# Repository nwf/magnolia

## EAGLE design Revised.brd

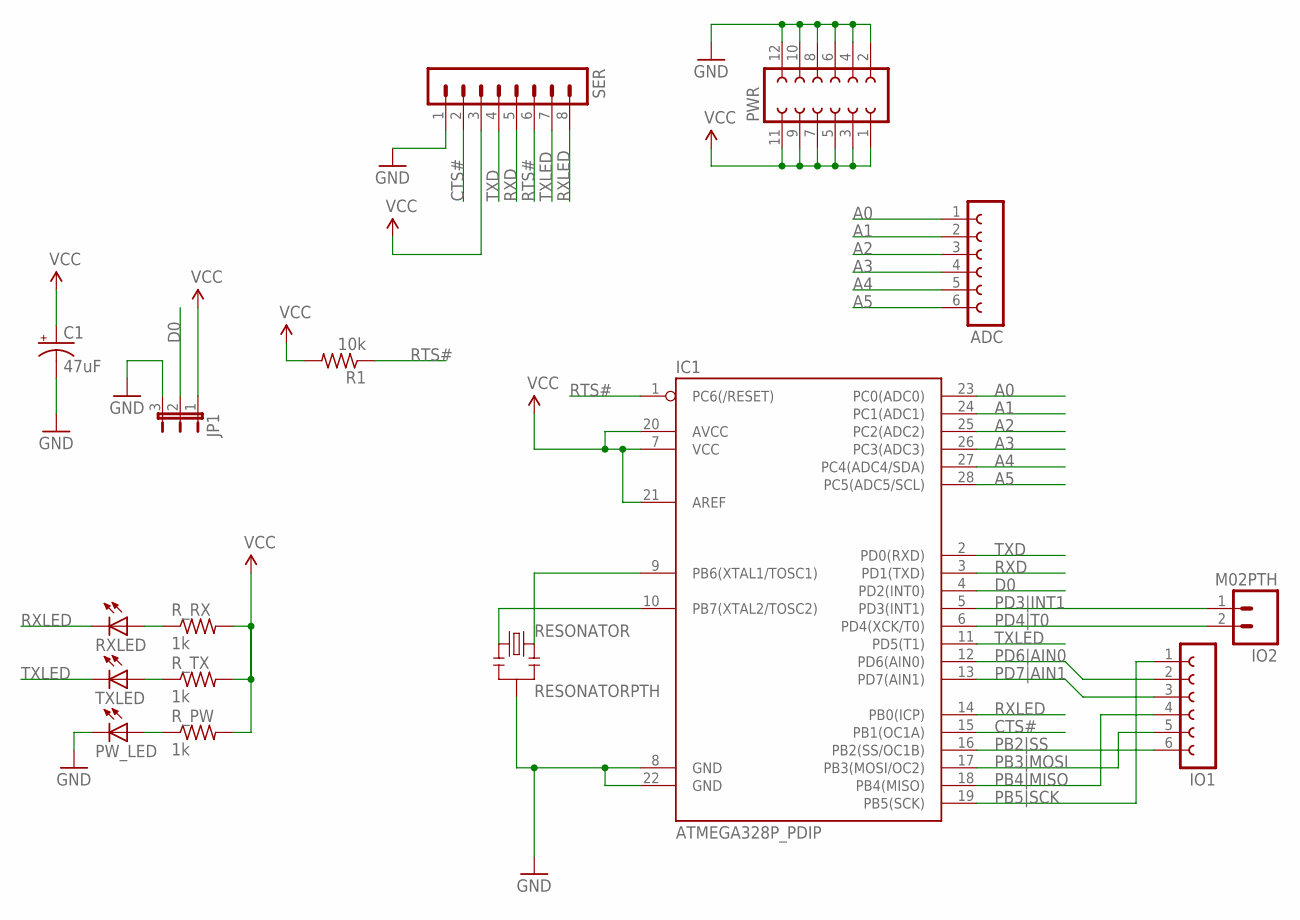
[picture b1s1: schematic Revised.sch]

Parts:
ADC: FE06-1; FE06
C1: 47uF; E2,5-6E
IC1: ATMEGA328P_PDIP; DIL28-3
IO1: FE06-1; FE06
IO2: M02PTH; 1X02
JP1: JP2E; JP2
PWR: FE06-2
PW_LED: LED5MM
R1: 10k; R0805
RESONATOR: RESONATORPTH; RESONATOR-PTH
RXLED: LED5MM
R_PW: 1k; R0805
R_RX: 1k; R0805
R_TX: 1k; R0805
SER: MA08-1W
TXLED: LED5MM

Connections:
A0: ADC.1, IC1.23 (PC0(ADC0))
A1: ADC.2, IC1.24 (PC1(ADC1))
A2: ADC.3, IC1.25 (PC2(ADC2))
A3: ADC.4, IC1.26 (PC3(ADC3))
A4: ADC.5, IC1.27 (PC4(ADC4/SDA))
A5: ADC.6, IC1.28 (PC5(ADC5/SCL))
CTS#: IC1.15 (PB1(OC1A)), SER.2
D0: IC1.4 (PD2(INT0)), JP1.2
GND: C1.-, IC1.8 (GND), IC1.22 (GND), JP1.3, PWR.2, PWR.4, PWR.6, PWR.8, PWR.10, PWR.12, PW_LED.K (C), RESONATOR.2, SER.1
unnamed: IC1.9 (PB6(XTAL1/TOSC1)), RESONATOR.3
unnamed: IC1.10 (PB7(XTAL2/TOSC2)), RESONATOR.1
unnamed: R_TX.1, TXLED.A
unnamed: RXLED.A, R_RX.1
unnamed: PW_LED.A, R_PW.1
PB2|SS: IC1.16 (PB2(SS/OC1B)), IO1.6
PB3|MOSI: IC1.17 (PB3(MOSI/OC2)), IO1.5
PB4|MISO: IC1.18 (PB4(MISO)), IO1.4
PB5|SCK: IC1.19 (PB5(SCK)), IO1.1
PD3|INT1: IC1.5 (PD3(INT1)), IO2.1
PD4|T0: IC1.6 (PD4(XCK/T0)), IO2.2
PD6|AIN0: IC1.12 (PD6(AIN0)), IO1.2
PD7|AIN1: IC1.13 (PD7(AIN1)), IO1.3
RTS#: IC1.1 (PC6(/RESET)), R1.1, SER.6
RXD: IC1.3 (PD1(TXD)), SER.5
RXLED: IC1.14 (PB0(ICP)), RXLED.K (C), SER.8
TXD: IC1.2 (PD0(RXD)), SER.4
TXLED: IC1.11 (PD5(T1)), SER.7, TXLED.K (C)
VCC: C1.+, IC1.7 (VCC), IC1.20 (AVCC), IC1.21 (AREF), JP1.1, PWR.1, PWR.3, PWR.5, PWR.7, PWR.9, PWR.11, R1.2, R_PW.2, R_RX.2, R_TX.2, SER.3

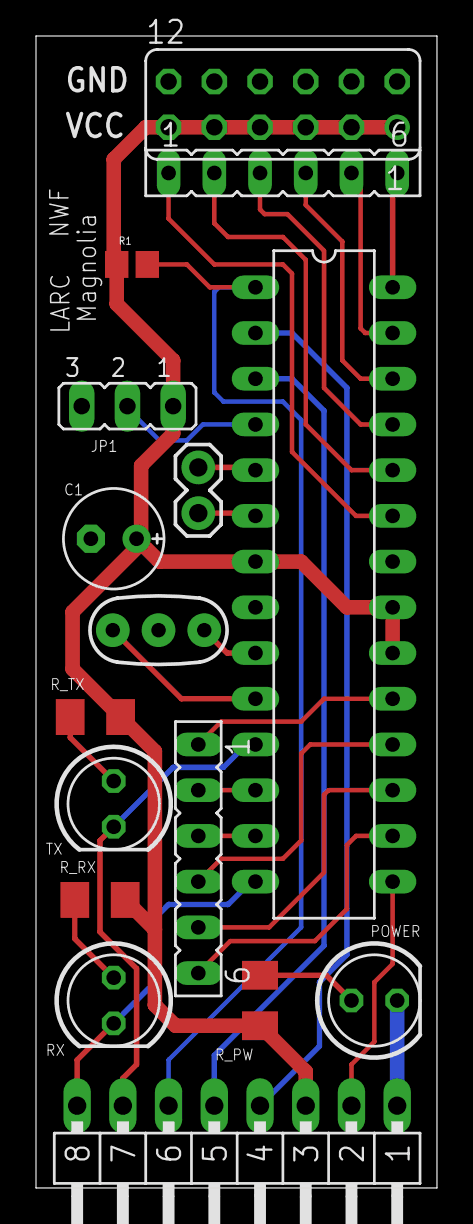
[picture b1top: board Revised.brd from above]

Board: 2 copper layers, 22.3 x 64.0 mm, 16 parts (0 on the bottom side), 28 nets.

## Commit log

2014-03-22 Checkin shipped brd file
2014-03-22 Derived sch from shipped brd file
2014-03-22 Add proposed revision versions
2014-03-22 Small tweaks
    Remove capacitive coupling to RST#, which should enable debugWIRE
    Thicken the power and ground traces, tweaking routes for clearance
2014-04-04 Cleanup
    Change IO2 header pinouts to include the entire SPI bus
    Move LEDs to PD5 (T1) and PB0 (ICP)
    Move PB1 (OC1A) to CTS# connector
    Redo some traces to avoid vias
2014-04-04 Ground plane, better analog pin routing?

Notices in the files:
parts and their libraries:
SparkFun-Connectors: Licensing: Creative Commons ShareAlike 4.0 International - https://creativecommons.org/licenses/by-sa/4.0
SparkFun-DigitalIC: Licensing: CC v3.0 Share-Alike You are welcome to use this library for commercial purposes.
